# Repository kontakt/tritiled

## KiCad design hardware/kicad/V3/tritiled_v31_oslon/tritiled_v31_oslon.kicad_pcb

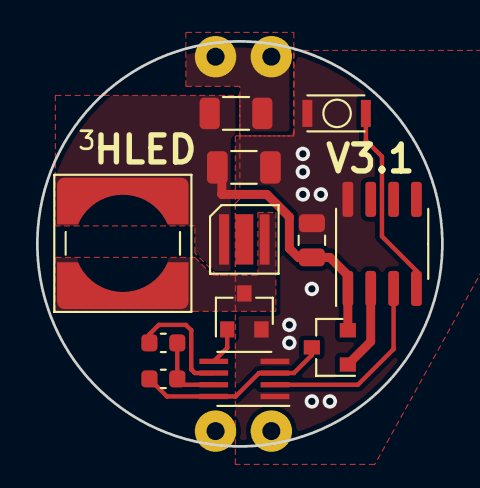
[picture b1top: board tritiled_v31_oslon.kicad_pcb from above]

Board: 2 copper layers, 22.5 x 22.5 mm, 13 parts (1 on the bottom side), 11 nets.

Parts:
B1: BAT-HLD-0010-THM_CR2032; BAT-HLD-001-THM
C2: 1uF; C_0805_2012Metric
C3: 10uF; C_1206_3216Metric
C5: 100nF; C_0603_1608Metric
D1: OSLON SV; OSLON-LV
IC1: PIC12LF1571; SOIC-8_3.9x4.9mm_P1.27mm
IC2: 74LVC1G123; SSOP-8_2.95x2.8mm_P0.65mm
L1: 1mH; Bourns-SRR6028
Q1: IRLML62244; SOT-23
Q2: DMG2305UX; SOT-23
R2: 100; R_1206_3216Metric
R3: 51k; C_0603_1608Metric
SW1: SMD_SWITCH3020; KXT-321-LHS

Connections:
+3V0: C2.1, C3.1, D1.1, IC1.1, L1.1, Q2.2, R2.1
GND: B1.2, C2.2, C3.2, IC1.8, IC2.1, IC2.4, Q1.2, SW1.1
unnamed: B1.1, R2.2
unnamed: C5.1, IC2.7, R3.2
unnamed: C5.2, IC2.6
unnamed: D1.2, L1.2, Q1.3
unnamed: IC1.2, Q2.1
unnamed: IC1.3, IC2.2
unnamed: IC1.4, SW1.2
unnamed: IC2.5, Q1.1
VCC: IC2.3, IC2.8, Q2.3, R3.1

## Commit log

2021-02-11 Add v3 case for Oslon Signal Verde
2021-02-14 Add KiCAD version
    OSRAM Oslon Signal Verde
